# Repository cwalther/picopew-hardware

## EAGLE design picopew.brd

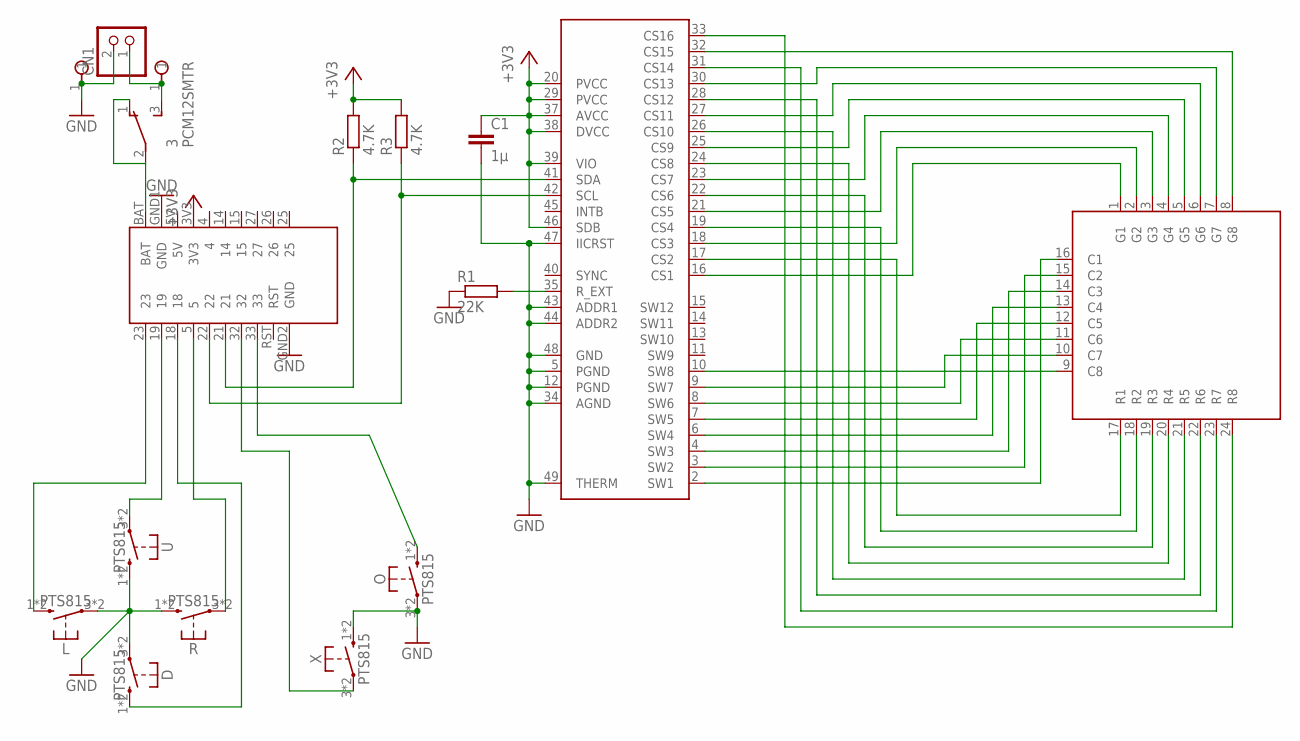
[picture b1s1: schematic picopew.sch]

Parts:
1: KYX-788AHG
2: TINYPICO
3: PCM12SMTR; MICROSLIDESWITCH
4, 5: SINGLEPAD
C1: 1µ; C0805
CN1: JST_2PIN-SMT-RA; JST-PH-2-SMT-RA
D: PTS815; MICROPUSHBUTTON
L: PTS815; MICROPUSHBUTTON
O: PTS815; MICROPUSHBUTTON
R: PTS815; MICROPUSHBUTTON
R1: 22K; R0805
R2, R3: 4.7K; R0805
U: PTS815; MICROPUSHBUTTON
U1: IS31FL3733-TQLS4; TQFP48
X: PTS815; MICROPUSHBUTTON

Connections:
5V: 2.5V
+3V3: 2.3V3, C1.1, R2.2, R3.2, U1.20 (PVCC), U1.29 (PVCC), U1.37 (AVCC), U1.38 (DVCC), U1.39 (VIO), U1.46 (SDB)
GND: 2.GND1 (GND), 2.GND2 (GND), 5.1, C1.2, CN1.2 (1), D.3, D.4, L.3, L.4, O.3, O.4, R.1 (S), R.2 (S), R1.1, U.1 (S), U.2 (S), U1.5 (PGND), U1.12 (PGND), U1.34 (AGND), U1.43 (ADDR1), U1.44 (ADDR2), U1.47 (IICRST), U1.48 (GND), U1.49 (THERM), X.1 (S), X.2 (S)
unnamed: 1.16 (C1), U1.2 (SW1)
unnamed: 1.15 (C2), U1.3 (SW2)
unnamed: 1.14 (C3), U1.4 (SW3)
unnamed: 1.13 (C4), U1.6 (SW4)
unnamed: 1.12 (C5), U1.7 (SW5)
unnamed: 1.11 (C6), U1.8 (SW6)
unnamed: 1.10 (C7), U1.9 (SW7)
unnamed: 1.9 (C8), U1.10 (SW8)
unnamed: 1.1 (G1), U1.16 (CS1)
unnamed: 1.17 (R1), U1.17 (CS2)
unnamed: 1.2 (G2), U1.18 (CS3)
unnamed: 1.18 (R2), U1.19 (CS4)
unnamed: 1.3 (G3), U1.21 (CS5)
unnamed: 1.19 (R3), U1.22 (CS6)
unnamed: 1.4 (G4), U1.23 (CS7)
unnamed: 1.20 (R4), U1.24 (CS8)
unnamed: 1.5 (G5), U1.25 (CS9)
unnamed: 1.21 (R5), U1.26 (CS10)
unnamed: 1.6 (G6), U1.27 (CS11)
unnamed: 1.22 (R6), U1.28 (CS12)
unnamed: 1.7 (G7), U1.30 (CS13)
unnamed: 1.23 (R7), U1.31 (CS14)
unnamed: 1.8 (G8), U1.32 (CS15)
unnamed: 1.24 (R8), U1.33 (CS16)
unnamed: 2.21, R2.1, U1.41 (SDA)
unnamed: 2.22, R3.1, U1.42 (SCL)
unnamed: R1.2, U1.35 (R_EXT)
unnamed: 2.33, O.1 (S), O.2 (S)
unnamed: 2.32, X.3, X.4
unnamed: 2.BAT, 3.1 (O), 3.2
unnamed: 3.3 (S), 4.1, CN1.1 (2)
unnamed: 2.5, R.3, R.4
unnamed: 2.18, D.1 (S), D.2 (S)
unnamed: 2.19, U.3, U.4
unnamed: 2.23, L.1 (S), L.2 (S)

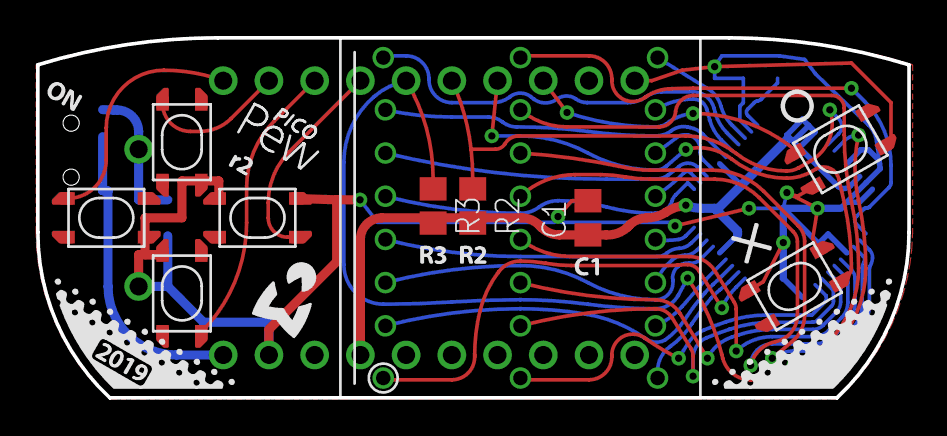
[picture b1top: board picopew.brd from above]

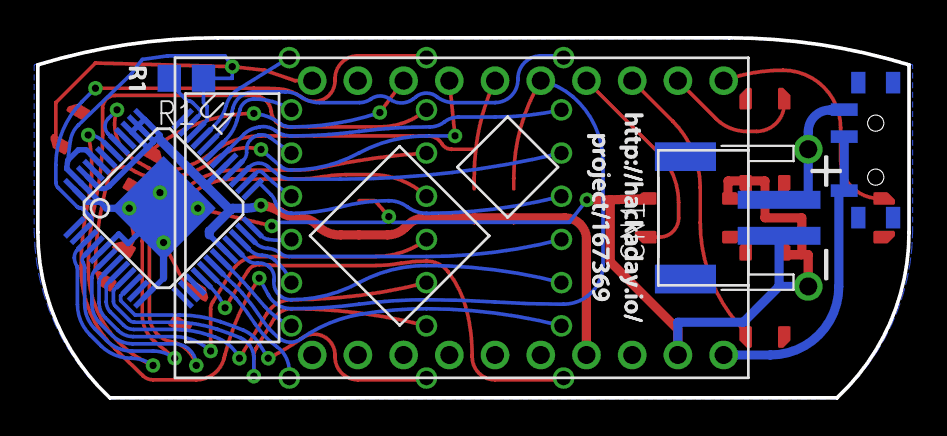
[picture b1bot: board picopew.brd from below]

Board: 2 copper layers, 48.4 x 20.0 mm, 74 parts (42 on the bottom side), 37 nets.

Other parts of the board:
U$1: PICOPEW-O
U$2: PICOPEW-CORNER-L
U$3: PICOPEW-X
U$4: PLUS
U$5: PICOPEW
U$6, U$72: CHAR114
U$7: CWLOGO-4
U$8: PICOPEW-CORNER-R
U$9, U$15, U$21: CHAR050
U$10: CHAR079
U$11: CHAR078
U$12: MINUS
U$14, U$20, U$22: CHAR082
U$16: CHAR048
U$17, U$19, U$25, U$26: CHAR049
U$18, U$31: CHAR057
U$23, U$29: CHAR051
U$24: CHAR067
U$27, U$30: CHAR054
U$28: CHAR055
U$52, U$59: CHAR104
U$53, U$54, U$77: CHAR116
U$55, U$71: CHAR112
U$56: CHAR058
U$57, U$58, U$70, U$78: CHAR047
U$60, U$63, U$65: CHAR097
U$61, U$76: CHAR099
U$62: CHAR107
U$64: CHAR100
U$66: CHAR121
U$67: CHAR046
U$68: CHAR105
U$69, U$73: CHAR111
U$74: CHAR106
U$75: CHAR101

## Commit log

2019-08-20 Routed and prettified layout.
2019-08-28 Silkscreen labeling and decorations.
2019-11-03 Larger drill for the headers and smaller vias.
2019-11-03 Move the outer pins of the LED matrix 0.15 mm farther out.
    As far as the DRC allows.
2019-11-03 Add JST connector footprint for those who want to connect their battery that way.
2019-11-03 Move R2 and R3 to be more centered under the LED matrix.
    Hoping this reduces the likelihood that the resistors will prevent the matrix from sitting flush on the board.
2019-11-13 Add 3D-printed enclosure design.
2019-11-16 Tweaks to the enclosure from the first print.
    - Deepen switch cutout – 1.6 mm is the correct depth, but for some reason (springback by the cantilevered shape?) it turned out only 1.1 mm – trying 2.0 mm now.
    - USB cutout corners can be rounded more, should reduce sagging of the bridge.
    - Move the right rail by 0.1 mm for tighter fit.
    - Add holes for LEDs.
    - Edges redone in a more rounded way for a more pleasant look and feel.
2019-11-17 Add license.
